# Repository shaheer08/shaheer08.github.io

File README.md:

## Hello People 

- [Fab Lab Workshop](https://shaheer08.github.io/test23)

- [FantaCode Internship](https://shaheer08.github.io/internship.github.io/)

### About Me
_I am An Engineering Student Pursuing B.Tech in Electronics And Communication Engineering_.

### Follow Me

### Support or Contact
**Muhammed Shaheer C**

 shaheerwyd@gmail.com

 +91 8111838406

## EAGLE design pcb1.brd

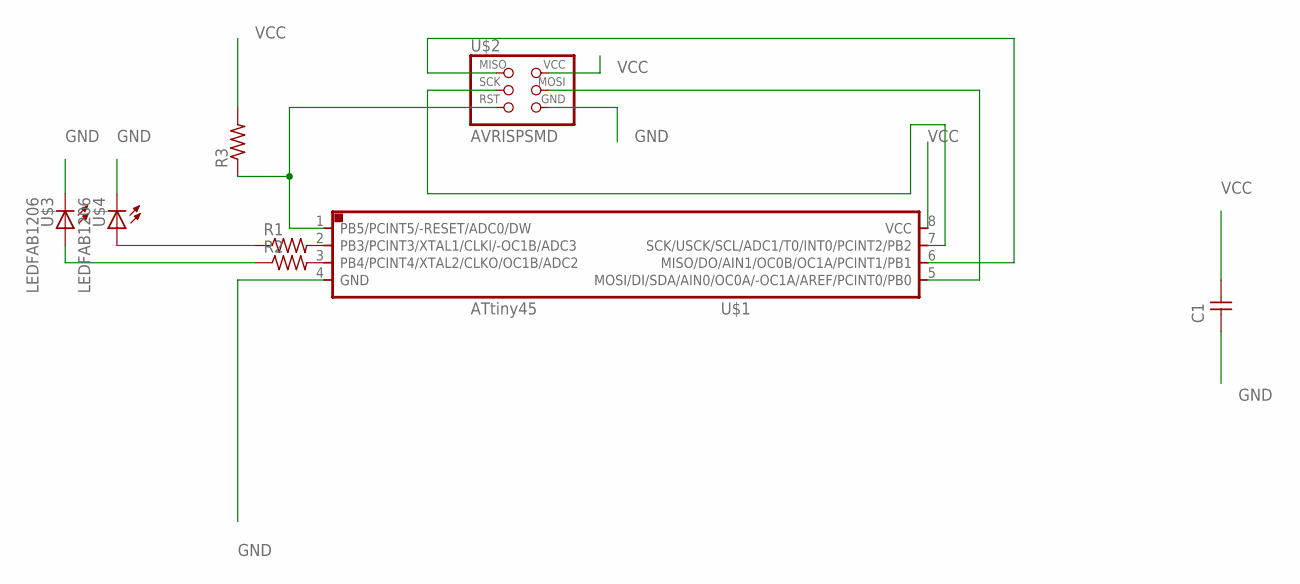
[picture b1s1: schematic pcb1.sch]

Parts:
C1: CAP-UNPOLARIZED; C1206
R1, R2, R3: RES-US1206FAB; R1206FAB
U$1: ATTINY45SI; SOIC8
U$2: AVRISPSMD; 2X03SMD
U$3, U$4: LEDFAB1206; LED1206FAB

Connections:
GND: C1.1, U$1.4 (GND), U$2.6 (GND), U$3.2 (C), U$4.2 (C)
unnamed: U$1.6 (MISO/DO/AIN1/OC0B/OC1A/PCINT1/PB1), U$2.1 (MISO)
unnamed: R1.2, U$1.2 (PB3/PCINT3/XTAL1/CLKI/-OC1B/ADC3)
unnamed: U$1.7 (SCK/USCK/SCL/ADC1/T0/INT0/PCINT2/PB2), U$2.3 (SCK)
unnamed: R3.1, U$1.1 (PB5/PCINT5/-RESET/ADC0/DW), U$2.5 (RST)
unnamed: R2.2, U$1.3 (PB4/PCINT4/XTAL2/CLKO/OC1B/ADC2)
unnamed: R1.1, U$4.1 (A)
unnamed: U$1.5 (MOSI/DI/SDA/AIN0/OC0A/-OC1A/AREF/PCINT0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), U$2.4 (MOSI)
unnamed: R2.1, U$3.1 (A)
VCC: C1.2, R3.2, U$1.8 (VCC), U$2.2 (VCC)

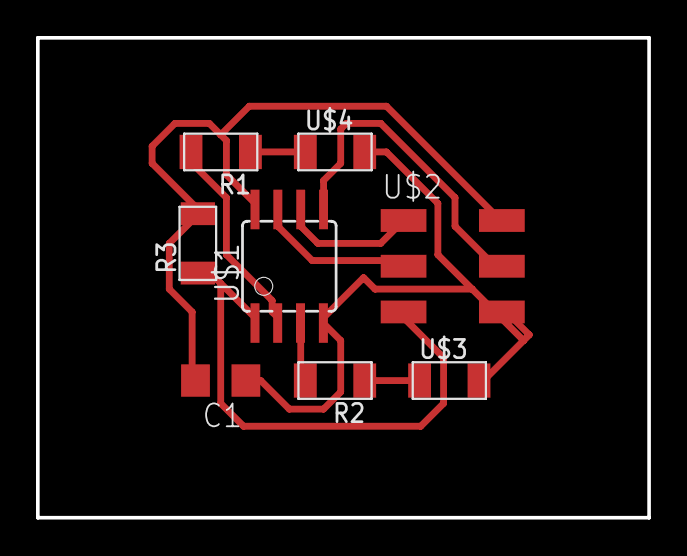
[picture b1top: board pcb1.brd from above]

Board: 2 copper layers, 34.0 x 26.7 mm, 8 parts (0 on the bottom side), 10 nets.

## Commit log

2017-08-03 Set theme jekyll-theme-slate
2017-08-03 Set theme jekyll-theme-modernist
2017-08-03 Set theme jekyll-theme-architect
2017-08-04 Create day 1
2017-08-10 Set theme jekyll-theme-cayman
